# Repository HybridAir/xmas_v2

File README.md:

# xmas_v2
The successor to last year's Xmas_v1 project
https://hackaday.io/project/8287-xmasv2

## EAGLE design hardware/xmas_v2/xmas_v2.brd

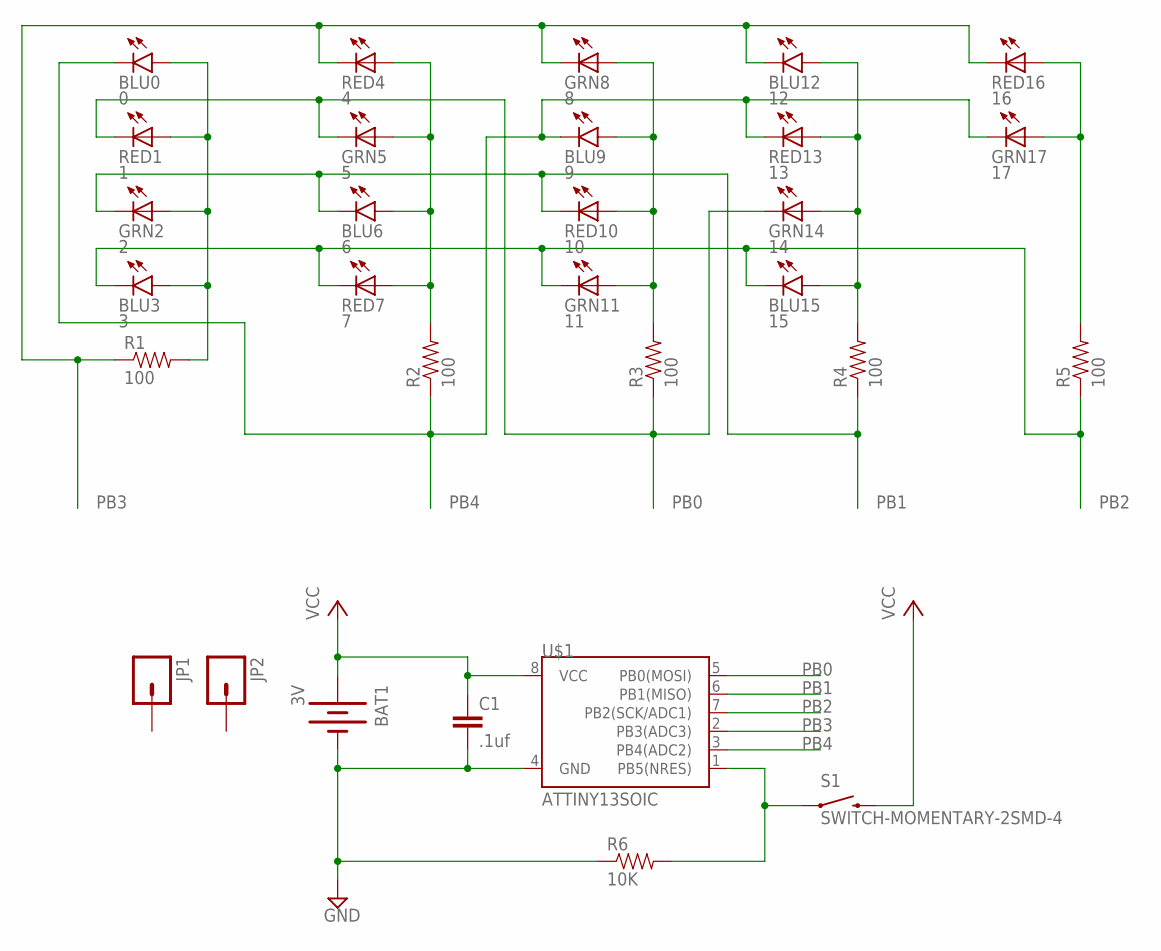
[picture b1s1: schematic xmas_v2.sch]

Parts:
BAT1: 3V; BATTCOM_20MM_PTH
BLU0: 0; LED5MM-KIT
BLU3: 3; LED5MM-KIT
BLU6: 6; LED5MM-KIT
BLU9: 9; LED5MM-KIT
BLU12: 12; LED5MM-KIT
BLU15: 15; LED5MM-KIT
C1: .1uf; 0805
GRN2: 2; CHIPLED_0805
GRN5: 5; CHIPLED_0805
GRN8: 8; CHIPLED_0805
GRN11: 11; CHIPLED_0805
GRN14: 14; CHIPLED_0805
GRN17: 17; CHIPLED_0805
JP1, JP2: M01NOSILK-KIT; 1X01NS-KIT
R1, R2, R3, R4, R5: 100; 0805
R6: 10K; 0805
RED1: 1; CHIPLED_0805
RED4: 4; CHIPLED_0805
RED7: 7; CHIPLED_0805
RED10: 10; CHIPLED_0805
RED13: 13; CHIPLED_0805
RED16: 16; CHIPLED_0805
S1: SWITCH-MOMENTARY-2SMD-4; TACTILE_SWITCH_TALL
U$1: ATTINY13SOIC; SO08

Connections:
GND: BAT1.2 (-), C1.2, R6.1, U$1.4 (GND)
unnamed: BLU0.A, BLU3.A, GRN2.A, R1.2, RED1.A
unnamed: BLU6.A, GRN5.A, R2.2, RED4.A, RED7.A
unnamed: BLU9.A, GRN8.A, GRN11.A, R3.2, RED10.A
unnamed: BLU12.A, BLU15.A, GRN14.A, R4.2, RED13.A
unnamed: GRN17.A, R5.2, RED16.A
unnamed: R6.2, S1.A2 (1), U$1.1 (PB5(NRES))
PB0: GRN5.C, GRN14.C, R3.1, RED1.C, U$1.5 (PB0(MOSI))
PB1: BLU6.K (C), GRN2.C, R4.1, RED10.C, U$1.6 (PB1(MISO))
PB2: BLU3.K (C), BLU15.K (C), GRN11.C, R5.1, RED7.C, U$1.7 (PB2(SCK/ADC1))
PB3: BLU12.K (C), GRN8.C, R1.1, RED4.C, RED16.C, U$1.2 (PB3(ADC3))
PB4: BLU0.K (C), BLU9.K (C), GRN17.C, R2.1, RED13.C, U$1.3 (PB4(ADC2))
VCC: BAT1.1 (+), C1.1, S1.B2 (2), U$1.8 (VCC)

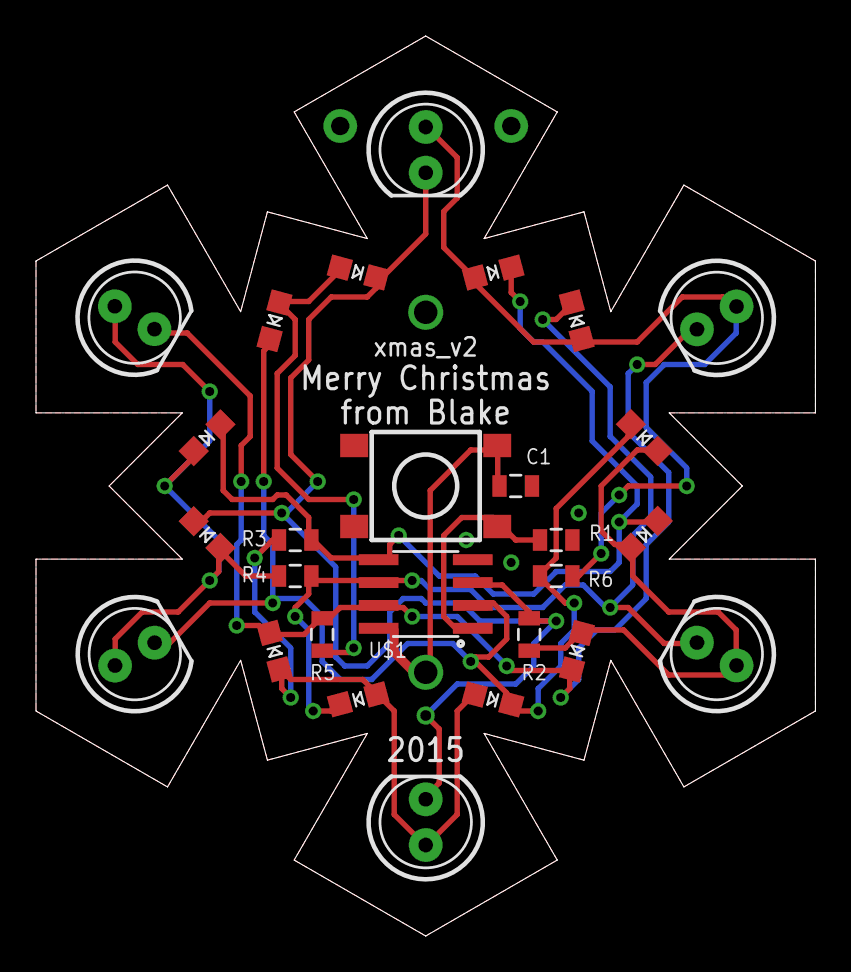
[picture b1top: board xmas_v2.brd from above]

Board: 2 copper layers, 43.3 x 50.0 mm, 30 parts (1 on the bottom side), 13 nets.

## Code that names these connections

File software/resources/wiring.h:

/*
*** Core13 ***
Arduino core designed for Attiny13 and similar devices.
NO WARRANTEE OR GUARANTEES!
Written by John "smeezekitty" 
You are free to use, redistribute and modify at will EXCEPT IF MARKED OTHERWISE IN A PARTICULAR SOURCE FILE!
Version 0.22
// ATMEL ATTINY13 - ARDUINO
//
//                  +-\/-+
// AinX (D X) PB5  1|    |8  Vcc
// AinX (D X) PB3  2|    |7  PB2 (D X)  AinX
// AinX (D X) PB4  3|    |6  PB1 (D X) PWM
//            GND  4|    |5  PB0 (D X) PWM
//                  +----+
*/
#ifndef Wiring_h
#define Wiring_h
#include <avr/io.h>
#include <stdlib.h>
#ifdef __cplusplus
extern "C"{
#endif
#define HIGH 1
#define LOW 0
#define INPUT 0
#define OUTPUT 1
#define false 0
#define FALSE 0
#define TRUE 1
#define true 1
#define PI 3.1416
#define HALF_PI 1.57
#define TWO_PI 6.283
#define DEG_TO_RAD 0.0174533
#define RAD_TO_DEG 57.2958
#define SERIAL 0
#define DISPLAY 1 //WTF are these?
#define LSBFIRST 0
#define MSBFIRST 1
#define CHANGE 1
#define FALLING 2
#define RISING 3
#define INTERNAL 1
#define EXTERNAL 0
#define DEFAULT 0
#ifdef abs
#undef abs
#endif
#define min(a,b) ((a)<(b)?(a):(b))
#define max(a,b) ((a)>(b)?(a):(b))
#define abs(x) ((x)>0?(x):-(x))
#define constrain(amt,low,high) ((amt)<(low)?(low):((amt)>(high)?(high):(amt)))
#define round(x)     ((x)>=0?(long)((x)+0.5):(long)((x)-0.5))
#define radians(deg) ((deg)*DEG_TO_RAD)
#define degrees(rad) ((rad)*RAD_TO_DEG)
#define sq(x) ((x)*(x))
#define interrupts() sei()
#define noInterrupts() cli()
#define clockCyclesPerMicrosecond() ( F_CPU / 1000000L )
#define clockCyclesToMicroseconds(a) ( ((a) * 1000L) / (F_CPU / 1000L) )
#define microsecondsToClockCycles(a) ( ((a) * (F_CPU / 1000L)) / 1000L )
#define lowByte(w) ((uint8_t) ((w) & 0xff))
#define highByte(w) ((uint8_t) ((w) >> 8))
#define bitRead(value, bit) (((value) >> (bit)) & 0x01)
#define bitSet(value, bit) ((value) |= (1UL << (bit)))
#define bitClear(value, bit) ((value) &= ~(1UL << (bit)))
#define bitWrite(value, bit, bitvalue) (bitvalue ? bitSet(value, bit) : bitClear(value, bit))
typedef unsigned int word;
#define bit(b) (1UL << (b))
typedef uint8_t boolean;
typedef uint8_t byte;
void init(void);
void pinMode(uint8_t, uint8_t);
void digitalWrite(uint8_t, uint8_t);
uint8_t digitalRead(uint8_t);
int analogRead(uint8_t); 
void analogReference(uint8_t mode);
void analogWrite(uint8_t, uint8_t);


void resetMillis(void);


unsigned long millis(void);
unsigned long micros(void);
void delay(unsigned ms);
void delayMicroseconds(int us);
void shiftOut(uint8_t, uint8_t, uint8_t, uint8_t);
uint8_t shiftIn(uint8_t, uint8_t, uint8_t);
unsigned long pulseIn(unsigned char pin, unsigned char stat, unsigned long timeout);
//void attachInterrupt(uint8_t, void (*)(void), int mode);
//void detachInterrupt(uint8_t);
void setup(void);
void loop(void);
#ifdef __cplusplus
} // extern "C"
#endif
#endif

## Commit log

2015-10-31 Initial creation
2015-10-31 Basic blinky stuff
2015-11-01 I managed to get io on the reset pin working so that's something
2015-11-01 Got button animation switching and sleep working
2015-11-03 Began implementing basic charleplexing code
    I have been working towards this all day, it compiles to 376 bytes so
    far
2015-11-03 Reintegrated basic sleep code
    642 bytes compiled
2015-11-03 Added a new animation
    808 bytes with that and the rest of the sleep code
2015-11-03 Got very basic POV working
2015-11-03 Expanded on existing animations and added centralized "frame" timing control
    966 bytes compiled
2015-11-04 Just about finalized the first 4 animations
2015-11-04 Added a new animation
    958 bytes compiled
2015-11-04 Moved the led code over to where it belongs
2015-11-05 Added mostly untested sleep timer code
2015-11-06 Got auto sleeping working
    Also modified some of the core13 files so I can reset the millis()
    value, compiles to 918 bytes
2015-11-06 Fixed the led brightness inconsistency in animation 5, but it's too dim now
    928 bytes
2015-11-06 Fixed the brightness problem for sure now
    Still need to test the other animations, also size is now 956 bytes
2015-11-06 Replaced delay with _delay_ms
    it compiles to 940 bytes now
2015-11-07 Cleaned up a lot, optimized what I could, I fixed sleep code
    compiles to 992 bytes and works with reset pin disabled
2015-11-07 ADC is off by default, don't need to tell it again
    saved 2 bytes, 990 compiled
2015-11-07 Added the ability to easily disable auto sleep
    compiles to 1004 bytes
2015-11-07 Cleaned up code, added comments
    compiles to 994 bytes now
2015-11-08 Added all parts
2015-11-08 Added charlieplex schem
2015-11-08 Schematic is done
2015-11-08 Added PCB outline
2015-11-08 All LEDs and most parts have been aligned
2015-11-09 Finished routing
2015-11-10 Minor routing changes
2015-11-12 Pretty much ready to go
2015-11-12 Moved some stuff
2015-11-12 This was updated for some reason
2015-11-13 Created gerber files

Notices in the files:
parts and their libraries:
SparkFun-DigitalIC: Licensing: Creative Commons ShareAlike 4.0 International - https://creativecommons.org/licenses/by-sa/4.0
